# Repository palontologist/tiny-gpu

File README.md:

# tiny-gpu

A RISC-V-based GPU implementation in Verilog designed to explore and implement high-performance GPU architectures—from scalar cores and vector SIMD to cache hierarchies and graphics rasterization.

Built with ~20 files of fully documented Verilog, the project evolves through 7 development milestones: RV32IM scalar core, INT4/FP32 ML extensions, sparsity-aware execution, out-of-order ROB, L1 cache, graphics pipeline, and 128-bit vector SIMD. It includes verified matrix addition/multiplication and vector kernels with full simulation and execution traces.

### Table of Contents

- [Overview](#overview)
- [Architecture](#architecture)
  - [GPU](#gpu)
  - [Memory](#memory)
  - [Core](#core)
- [Hardware Implementation](#hardware-implementation)
- [ISA](#isa)
  - [Base RV32IM](#base-rv32im)
  - [Custom Extensions](#custom-extensions)
  - [Register File](#register-file)
- [Execution](#execution)
  - [Pipeline Stages](#pipeline-stages)
  - [Out-of-Order Execution](#out-of-order-execution)
  - [Sparsity-Aware Execution](#sparsity-aware-execution)
  - [Thread](#thread)
- [Kernels](#kernels)
  - [Matrix Addition](#matrix-addition-rv32i)
  - [Matrix Multiplication](#matrix-multiplication-rv32im)
  - [Vector DP4A](#vector-dp4a-phase-7--custom2)
- [Simulation](#simulation)
- [Optimizations](#optimizations)
  - [Implemented](#implemented-optimizations)
  - [Future](#future-optimizations)
- [Unified CPU/GPU Architecture (Approach B: RVV) & Modular Extensibility](#unified-cpugpu-architecture-approach-b-rvv--modular-extensibility)
- [Next Steps](#next-steps)

# Overview

While there are many resources for learning CPU architecture, GPU internals remain largely proprietary and opaque. Open-source implementations like [Miaow](https://github.com/VerticalResearchGroup/miaow) and [VeriGPU](https://github.com/hughperkins/VeriGPU/tree/main) are excellent but highly complex.

`tiny-gpu` is designed to bridge this gap, providing a transparent and modular reference implementation of a GPU's core logic.

## What is tiny-gpu?

> [!IMPORTANT]
> **tiny-gpu** is a RISC-V-based GPU implementation focused on the fundamental principles of GPGPU and ML-accelerator architectures. It emphasizes the general mechanisms of data parallelism and memory throughput rather than graphics-specific hardware.

The project is structured into 7 development milestones:

- **Phase 1**: RV32IM scalar core (RISC-V base ISA)
- **Phase 2**: INT4/FP32 custom extensions for ML inference
- **Phase 3**: Sparsity-aware execution (zero-skip for power efficiency)
- **Phase 4**: Out-of-order execution with Tomasulo-style ROB
- **Phase 5**: Per-thread L1 data cache (2-way set-associative)
- **Phase 6**: Graphics pipeline (rasterizer + texture unit + framebuffer)
- **Phase 7**: 128-bit vector extensions (INT8/INT4 SIMD, FP32 stubs)

The project explores four primary domains:
1. **Architecture** - Defining the core elements of a GPU and their interconnections.
2. **Parallelization** - Implementing the SIMD programming model in hardware.
3. **Memory** - Managing bandwidth constraints and latency via caching.
4. **ML Acceleration** - Utilizing vector units and quantization for efficient inference.

# Architecture

## GPU

`tiny-gpu` executes a single kernel at a time through the following process:
1. Load global program memory with kernel code (32-bit RV32IM instructions).
2. Load data memory with the necessary data (32-bit scalar or 128-bit vector).
3. Specify the thread count in the device control register.
4. Launch the kernel via the start signal.

The GPU architecture consists of:
1. Device control register
2. Dispatcher
3. Compute cores (each containing a ROB, L1 cache, and vector units)
4. Memory controllers for data and program memory
5. L1 data cache (per-thread, 2-way set-associative)

### GPU Parameters

| Parameter | Default | Description |
|-----------|---------|-------------|
| `NUM_CORES` | 2 | Number of compute cores |
| `THREADS_PER_BLOCK` | 4 | SIMD width per core |
| `ROB_DEPTH` | 16 | Reorder buffer entries per core |
| `L1_SETS` | 16 | L1 cache sets per thread |
| `VECTOR_ENABLE` | 1 | 128-bit data bus (0 = 32-bit legacy) |

### Device Control Register
The device control register stores metadata for kernel execution, primarily the `thread_count`—the total number of threads launched for the active kernel.

### Dispatcher
The dispatcher manages the distribution of threads to compute cores. It organizes threads into **blocks** and assigns them to available cores. Once all blocks are processed, the dispatcher signals kernel completion.

## Memory

`tiny-gpu` interfaces with an external global memory, separating data and program memory for architectural simplicity.

### Global Memory
- **Data Memory:** 8-bit addressability (256 word-addressable rows). Supports 32-bit scalar data or 128-bit vector data (when `VECTOR_ENABLE=1`).
- **Program Memory:** 8-bit addressability (256 word-addressable rows) storing 32-bit RV32IM instructions.

### Memory Controllers
The memory controllers manage outgoing requests from the compute cores, throttling access based on external memory bandwidth and relaying responses back to the requesting resource.

### L1 Data Cache
To mitigate global memory latency, each thread utilizes a **private L1 data cache** (Phase 5):
- **Organization:** 2-way set-associative (16 sets by default).
- **Policy:** Write-through (no dirty bits required).
- **Latency:** 1 cycle hit; memory-controller round-trip + 1 fill cycle for misses.
- **Replacement:** LRU (Least Recently Used) policy per set.

## Core

Each core manages a block of threads. To maximize resource utilization, the core provides a dedicated ALU, LSU, PC, scalar/vector register files, and L1 cache for each thread.

### Scheduler
A single scheduler manages the execution of threads through a 7-stage pipeline. The scheduler executes one block to completion, processing all threads in-sync and sequentially.

- **Sparsity-Aware Execution (Phase 3):** If all threads in a warp have zero-valued operands for an ALU operation, the scheduler skips the EXECUTE stage and writes zero directly to save power and cycles.
- **ROB Hazard Management (Phase 4):** Before advancing past the REQUEST stage, the scheduler checks for unresolved in-flight writes in the ROB. The pipeline stalls until the hazard clears or the value is forwarded.

### Reorder Buffer (ROB)
Phase 4 introduces a Tomasulo-style ROB for out-of-order execution:
- **In-order allocation** at the tail, **in-order commit** at the head.
- **Out-of-order writeback** upon execution unit completion.
- **Hazard detection** and **Result forwarding** to minimize pipeline stalls.

Each ROB entry covers one warp-level instruction, storing per-thread result data for SIMD execution.

### Fetcher
Asynchronously fetches 32-bit instructions from program memory based on the current PC.

### Decoder
Decodes RV32IM instructions into control signals, including:
- **Standard RV32I** opcodes.
- **RV32M** multiply/divide extensions.
- **Custom Opcodes:** `CUSTOM0` (RET), `CUSTOM1` (INT4/FP32), `CUSTOM2` (128-bit vector SIMD).

### Register Files
- **Scalar Registers (RV32):** 32 × 32-bit registers (x0-x31). x0 is hardwired to zero; x13-x15 are read-only special registers (`%blockIdx`, `%blockDim`, `%threadIdx`).
- **Vector Registers (Phase 7):** 16 × 128-bit registers (v0-v15). v0 is hardwired to zero; v13-v15 mirror scalar special registers.

### ALUs
Dedicated arithmetic-logic units per thread for scalar computations:
- **RV32I/M:** Full integer and multiply/divide support.
- **Custom (Phase 2/6):** `DP4A` (INT4 dot-product accumulate) and FP32 stubs.

### Vector ALUs (Phase 7)
Dedicated 128-bit vector ALUs for packed SIMD operations:
- **INT8:** 16-lane add, multiply, and multiply-accumulate.
- **INT4:** 4 × (8 × INT4 signed DP4A) for 32-bit accumulation.
- **FP32:** 4-lane add, multiply, and FMA (stubs).

### LSUs
Load-Store Units manage access to global data memory, supporting standard RV32I operations and Phase 7 vector extensions (`VLW.Q`, `VSW.Q` for 128-bit quad-word transfers).

### PCs
Dedicated program counters per thread. The PC increments by 4 for standard instructions or jumps to target addresses during branch/jump operations.

### Graphics Pipeline (Phase 6)
- **Rasterizer:** Scan-line tile rasterizer with barycentric interpolation (16.16 fixed-point).
- **Texture Unit:** Bilinear filtering with INT8 texels (8.8 fixed-point UV).
- **Framebuffer Interface:** Connects rasterizer output to display memory.

# Hardware Implementation

To move `tiny-gpu` from simulation to physical hardware, a custom carrier board has been designed. All design files, schematics, and assembly guides can be found in the [`/fpga_carrier_board_files`](/home/palontologist/Downloads/dev/tiny-gpu/fpga_carrier_board_files) directory.

### Target Platform
- **FPGA:** AMD Xilinx Artix-7 (XC7A100T-2FGG484I)
- **Memory:** DDR3L x16 (MT41K256M16TW-107:P) for high-bandwidth data access.
- **Video Output:** HDMI 1.4 via SII9022A transmitter.
- **Power:** USB-C PD input with multi-rail voltage regulation (1.0V, 1.8V, 1.35V, 3.3V).

### Design Workflow
The PCB was developed using a code-first approach via **Solder CLI**, allowing for rapid iteration of the 128-bit memory bus and signal integrity optimization. The final design is compatible with KiCad.

### Assembly & Bring-up
A detailed assembly guide (`fpga_carrier_board_GUIDE.md`) is provided, covering the 3D printing of enclosure mounts, BGA soldering of the FPGA and RAM, and the step-by-step bring-up process using a JTAG debugger.

# ISA

The architecture implements the **RV32IM** base ISA with custom extensions for GPU and ML workloads.

## Base RV32IM
Full support for standard RISC-V integer (`I`) and multiply/divide (`M`) instructions (LUI, AUIPC, JAL, JALR, BRANCH, LOAD, STORE, OP-IMM, OP, SYSTEM, MUL, DIV, etc.).

## Custom Extensions

| Opcode | Name | Description |
|--------|------|-------------|
| `CUSTOM0` | `RET` | Return from kernel execution |
| `CUSTOM1` | `DP4A` | INT4 4-element dot product with 32-bit accumulation |
| `CUSTOM1` | `FADD` / `FMUL` / `FFMA` | Single-precision floating point arithmetic stubs |
| `CUSTOM2` | `VADD` / `VMUL` / `VMAC` | 128-bit packed INT8 vector operations |
| `CUSTOM2` | `VDP4A` | 128-bit packed INT4 dot product accumulate |
| `CUSTOM2` | `VLW.Q` / `VSW.Q` | 128-bit vector quad-word memory load/store |

## Register File

- **Scalar Registers:** 32 registers (`x0` through `x31`).
  - `x0`: Constant 0
  - `x13`: Read-only `%blockIdx`
  - `x14`: Read-only `%blockDim`
  - `x15`: Read-only `%threadIdx`
- **Vector Registers:** 16 registers (`v0` through `v15`), each 128 bits wide.

# Execution

## Pipeline Stages

The execution pipeline consists of 7 stages:
1. **FETCH:** Retrieve instruction from program memory.
2. **DECODE:** Decode instruction and identify operand registers.
3. **REQUEST:** Issue memory requests or check for ROB hazards.
4. **WAIT:** Wait for memory data or hazard clearance.
5. **EXECUTE:** Compute ALU / Vector / Branch results (or perform zero-skip).
6. **UPDATE:** Update PC, write back results to register file or ROB.
7. **COMMIT:** In-order commit from ROB to architectural state.

## Out-of-Order Execution
Supported via Tomasulo-style Reorder Buffer (ROB) tracking in-flight instructions, resolving RAW hazards, and enabling speculative result forwarding.

## Sparsity-Aware Execution
Skips the execute stage when operands are detected as zero, directly writing zero to destination registers and cutting dynamic power consumption.

## Thread
Threads execute in SIMD blocks where each lane shares instruction flow but maintains private register and cache state.

# Kernels

### Matrix Addition (RV32I)
Demonstrates standard RISC-V scalar instructions distributed across threads to compute element-wise addition over matrix buffers.

### Matrix Multiplication (RV32IM)
Leverages RV32M hardware multiplier extensions for high-throughput tile-based matrix multiplication.

### Vector DP4A (Phase 7 / CUSTOM2)
Utilizes 128-bit vector units to compute quantized INT4 dot products with 32-bit accumulation for neural network linear layers.

# Simulation

### Prerequisites
- `iverilog` (Icarus Verilog)
- Python 3 & `cocotb`
- `gnumake`

```bash
# Using Nix
nix-shell -p iverilog python3 python3Packages.cocotb gnumake
```

### Run Tests
```bash
make test_matadd    # Scalar matrix addition
make test_matmul    # Scalar matrix multiplication + vector DP4A
```

# Optimizations

### Implemented Optimizations
- **INT4 Quantization:** Efficient ML inference with reduced precision.
- **Sparsity-Aware Skip:** Dynamic power optimization for zero operands.
- **Tomasulo ROB:** Dynamic out-of-order execution with result forwarding.
- **Per-Thread L1 Cache:** Mitigates global memory latency.
- **Vector SIMD:** 128-bit data bus with packed INT8/INT4 and FP32 stubs.

### Future Optimizations
- **Warp Scheduling:** Implement multi-warp concurrency per core.
- **Branch Divergence:** Handle divergent execution paths.
- **FP32 Silicon:** Replace stubs with IEEE-754 compliant FP IP.
- **Physical Bring-up:** Finalize fabrication and test the `tiny-gpu` on the custom Artix-7 carrier board.

# Unified CPU/GPU Architecture (Approach B: RVV) & Modular Extensibility

As `tiny-gpu` evolves, the architectural roadmap moves toward a **Unified RISC-V CPU/GPU Architecture** based on the standard **RISC-V Vector Extension (RVV 1.0)** and **Simple-V** dynamic vectorization.

### Why Unified RVV (Approach B)?
- **Vector-Length Agnostic (VLA):** Binary executables automatically scale across hardware vector widths ($VLEN$) without recompilation.
- **Standard Toolchains:** Upstream LLVM and GCC support, eliminating proprietary SIMT compiler forks.
- **Vulkan / SPIR-V Support:** Seamless translation of graphics shaders directly into standard vector instructions.

### Modular Extensibility & eGPU Scaling
- **Seamless Laptop-to-eGPU Offloading:** Identical binaries run locally on a low-power laptop core ($VLEN=128\text{b}$) and scale effortlessly to an external accelerator ($VLEN=2048\text{b}\text{ to }4096\text{b}$).
- **Coherent Interconnects:** Interfacing over CXL.mem/CXL.cache or TileLink/PCIe eliminates explicit PCIe data copies (`cudaMemcpy`) in favor of unified virtual memory.

📖 **Detailed Architectural Specification:** For the complete design document, pipeline diagrams, and roadmap, see [`docs/unified-cpu-gpu-rvv.md`](docs/unified-cpu-gpu-rvv.md).

## Next Steps
Contributors are welcome to help with the TODO list or submit PRs for new optimizations!

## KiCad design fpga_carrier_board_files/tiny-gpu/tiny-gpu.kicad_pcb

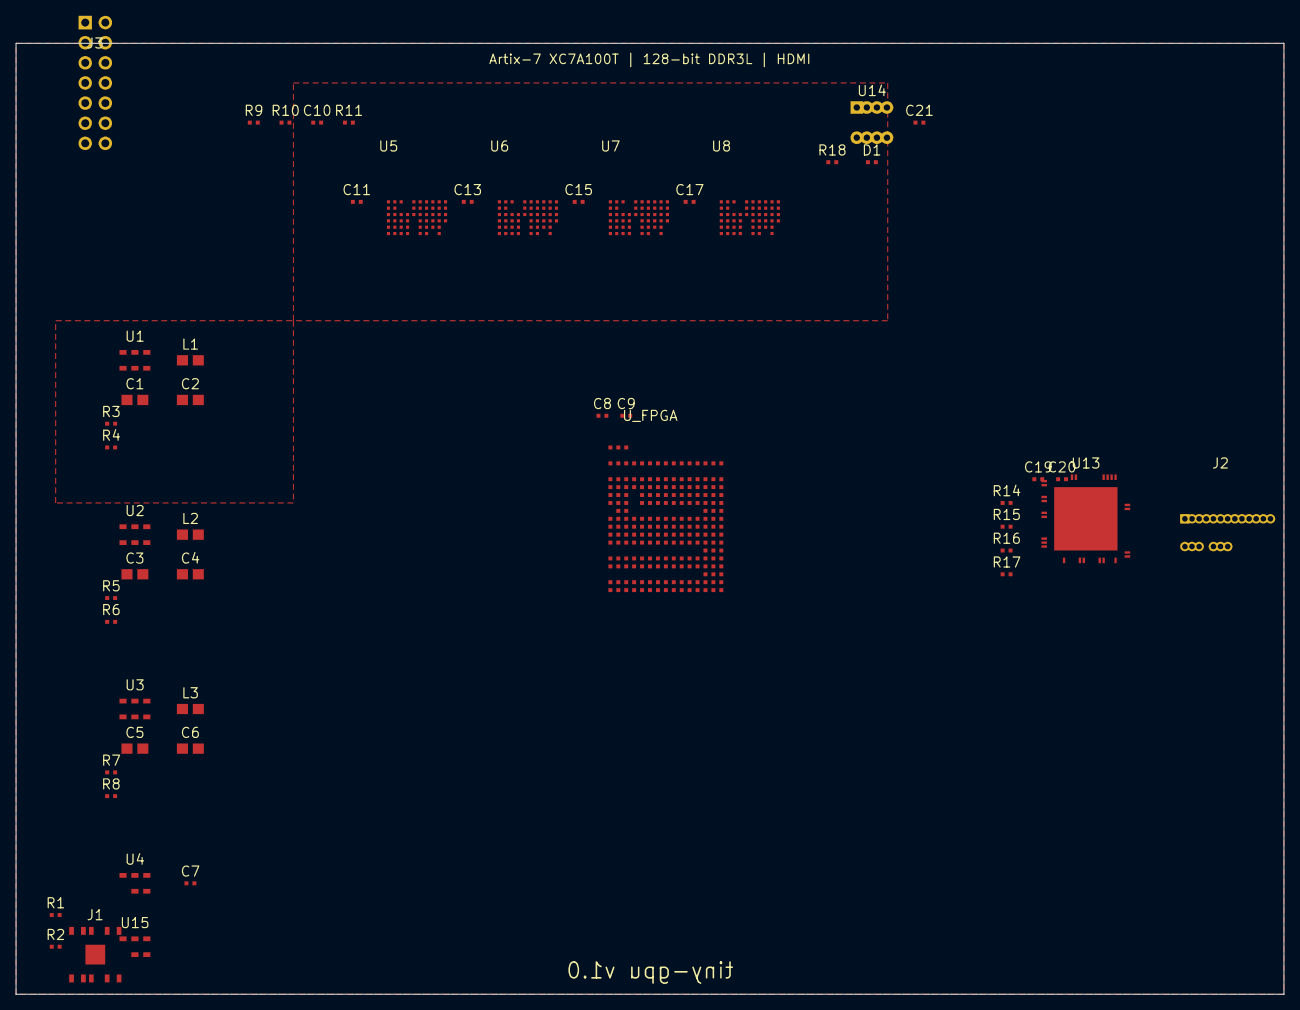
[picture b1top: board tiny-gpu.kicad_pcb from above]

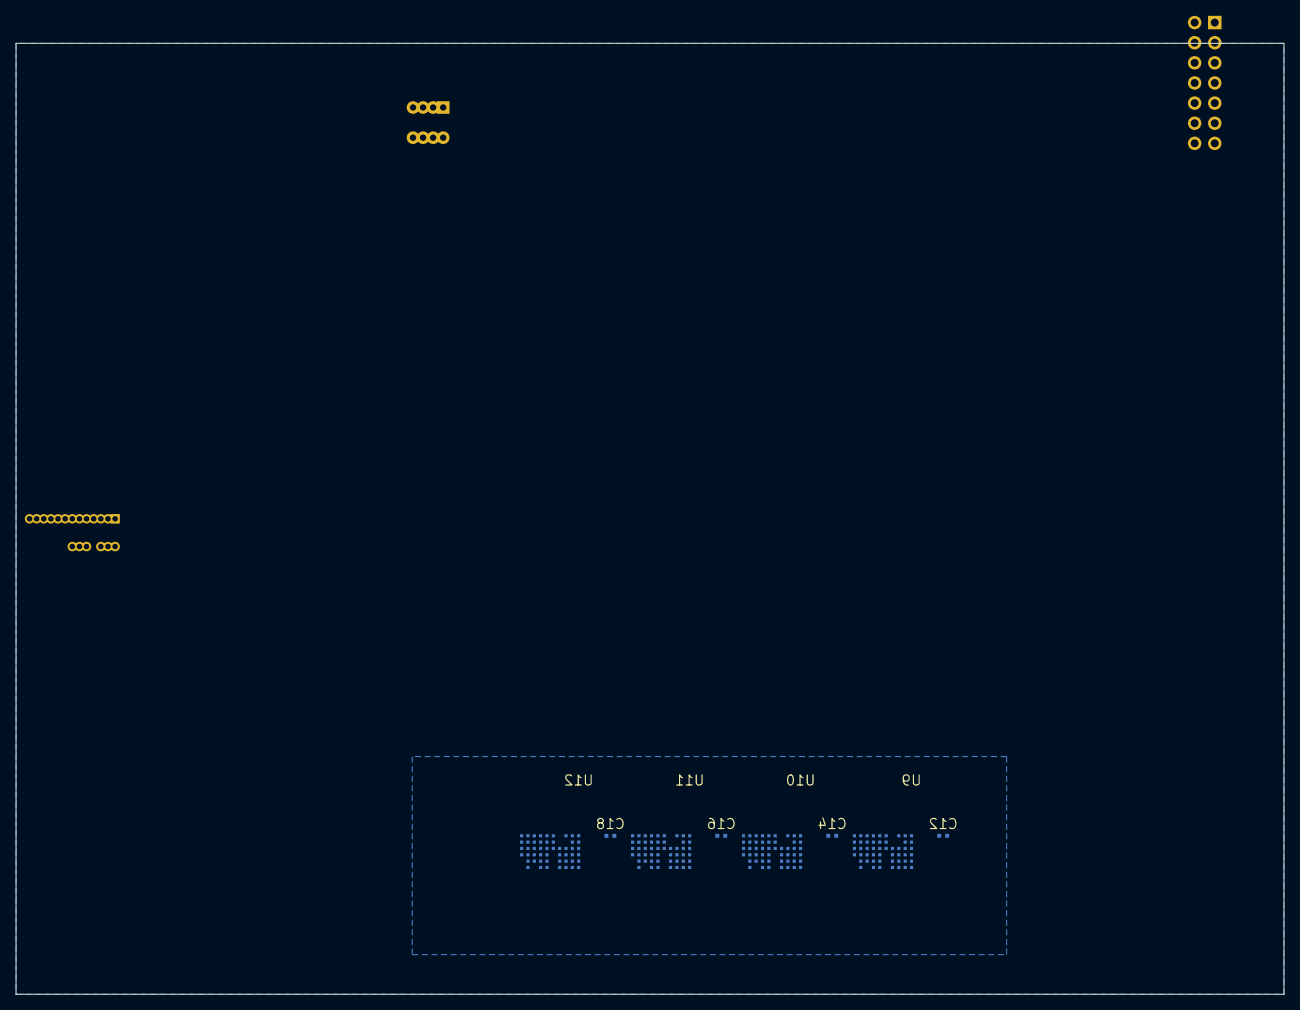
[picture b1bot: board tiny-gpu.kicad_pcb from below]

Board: 4 copper layers, 160.0 x 120.0 mm, 60 parts (8 on the bottom side), 226 nets, no tracks yet.

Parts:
C1, C2, C3, C4, C5, C6: C_0805_2012Metric
C7, C8, C9, C10, C11, C12, C13, C14, C15, C16, C17, C18, C19, C20, C21: C_0402_1005Metric
D1: LED_0402_1005Metric
J1: USB_C_Receptacle_GCT_USB4135-GF-A_Vertical
J2: HDMI_TypeA_Molex_2171100001_Horizontal
J3: PinHeader_2x07_P2.54mm_Vertical
L1, L2, L3: L_0805_2012Metric
R1, R2, R3, R4, R5, R6, R7, R8, R9, R10, R11, R14, R15, R16, R17, R18: R_0402_1005Metric
U1, U2, U3: SOT-23-6
U4, U15: SOT-25
U5, U6, U7, U8, U9, U10, U11, U12: BGA-96_9x12_8.0x10.5mm_Layout9x11_P0.8mm
U13: QFN-72-1EP_10x10mm_P0.5mm_EP8x8mm
U14: SOIC-8_3.9x4.9mm_P1.27mm
U_FPGA: BGA-484_23x23_21.0x21.0mm_Layout22x22_P0.95mm

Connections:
3V3_IO: C7.1, C19.1, C21.1, J2.18, J3.11, R14.1, R15.1, R16.1, R17.1, U4.4, U13.2, U14.3, U14.7, U14.8, U_FPGA.VCCO_14, U_FPGA.VCCO_15
CC1: J1.A5, R1.1
CC2: J1.B5, R2.1
DDR_A0: U5.A0, U6.A0, U7.A0, U8.A0, U9.A0, U10.A0, U11.A0, U12.A0, U_FPGA.DDR_A0
DDR_A1: U5.A1, U6.A1, U7.A1, U8.A1, U9.A1, U10.A1, U11.A1, U12.A1, U_FPGA.DDR_A1
DDR_A2: U5.A2, U6.A2, U7.A2, U8.A2, U9.A2, U10.A2, U11.A2, U12.A2, U_FPGA.DDR_A2
DDR_A3: U5.A3, U6.A3, U7.A3, U8.A3, U9.A3, U10.A3, U11.A3, U12.A3, U_FPGA.DDR_A3
DDR_A4: U5.A4, U6.A4, U7.A4, U8.A4, U9.A4, U10.A4, U11.A4, U12.A4, U_FPGA.DDR_A4
DDR_A5: U5.A5, U6.A5, U7.A5, U8.A5, U9.A5, U10.A5, U11.A5, U12.A5, U_FPGA.DDR_A5
DDR_A6: U5.A6, U6.A6, U7.A6, U8.A6, U9.A6, U10.A6, U11.A6, U12.A6, U_FPGA.DDR_A6
DDR_A7: U5.A7, U6.A7, U7.A7, U8.A7, U9.A7, U10.A7, U11.A7, U12.A7, U_FPGA.DDR_A7
DDR_A8: U5.A8, U6.A8, U7.A8, U8.A8, U9.A8, U10.A8, U11.A8, U12.A8, U_FPGA.DDR_A8
DDR_A9: U5.A9, U6.A9, U7.A9, U8.A9, U9.A9, U10.A9, U11.A9, U12.A9, U_FPGA.DDR_A9
DDR_A10: U5.A10, U6.A10, U7.A10, U8.A10, U9.A10, U10.A10, U11.A10, U12.A10, U_FPGA.DDR_A10
DDR_A11: U5.A11, U6.A11, U7.A11, U8.A11, U9.A11, U10.A11, U11.A11, U12.A11, U_FPGA.DDR_A11
DDR_A12: U5.A12, U6.A12, U7.A12, U8.A12, U9.A12, U10.A12, U11.A12, U12.A12, U_FPGA.DDR_A12
DDR_A13: U5.A13, U6.A13, U7.A13, U8.A13, U9.A13, U10.A13, U11.A13, U12.A13, U_FPGA.DDR_A13
DDR_BA0: U5.BA0, U6.BA0, U7.BA0, U8.BA0, U9.BA0, U10.BA0, U11.BA0, U12.BA0, U_FPGA.DDR_BA0
DDR_BA1: U5.BA1, U6.BA1, U7.BA1, U8.BA1, U9.BA1, U10.BA1, U11.BA1, U12.BA1, U_FPGA.DDR_BA1
DDR_BA2: U5.BA2, U6.BA2, U7.BA2, U8.BA2, U9.BA2, U10.BA2, U11.BA2, U12.BA2, U_FPGA.DDR_BA2
DDR_CAS_N: U5.CASN, U6.CASN, U7.CASN, U8.CASN, U9.CASN, U10.CASN, U11.CASN, U12.CASN, U_FPGA.DDR_CASN
DDR_CKE: U5.CKE, U6.CKE, U7.CKE, U8.CKE, U9.CKE, U10.CKE, U11.CKE, U12.CKE, U_FPGA.DDR_CKE
DDR_CKN: U5.CKN, U6.CKN, U7.CKN, U8.CKN, U9.CKN, U10.CKN, U11.CKN, U12.CKN, U_FPGA.DDR_CKN
DDR_CKP: U5.CKP, U6.CKP, U7.CKP, U8.CKP, U9.CKP, U10.CKP, U11.CKP, U12.CKP, U_FPGA.DDR_CKP
DDR_CS_N: U5.CSN, U6.CSN, U7.CSN, U8.CSN, U9.CSN, U10.CSN, U11.CSN, U12.CSN, U_FPGA.DDR_CSN
DDR_DM0: U5.DM, U_FPGA.DDR_DM0
DDR_DM1: U6.DM, U_FPGA.DDR_DM1
DDR_DM2: U7.DM, U_FPGA.DDR_DM2
DDR_DM3: U8.DM, U_FPGA.DDR_DM3
DDR_DM4: U9.DM, U_FPGA.DDR_DM4
DDR_DM5: U10.DM, U_FPGA.DDR_DM5
DDR_DM6: U11.DM, U_FPGA.DDR_DM6
DDR_DM7: U12.DM, U_FPGA.DDR_DM7
DDR_DQ0: U5.DQ0, U_FPGA.DDR_DQ0
DDR_DQ1: U5.DQ1, U_FPGA.DDR_DQ1
DDR_DQ2: U5.DQ2, U_FPGA.DDR_DQ2
DDR_DQ3: U5.DQ3, U_FPGA.DDR_DQ3
DDR_DQ4: U5.DQ4, U_FPGA.DDR_DQ4
DDR_DQ5: U5.DQ5, U_FPGA.DDR_DQ5
DDR_DQ6: U5.DQ6, U_FPGA.DDR_DQ6
DDR_DQ7: U5.DQ7, U_FPGA.DDR_DQ7
DDR_DQ8: U5.DQ8, U_FPGA.DDR_DQ8
DDR_DQ9: U5.DQ9, U_FPGA.DDR_DQ9
DDR_DQ10: U5.DQ10, U_FPGA.DDR_DQ10
DDR_DQ11: U5.DQ11, U_FPGA.DDR_DQ11
DDR_DQ12: U5.DQ12, U_FPGA.DDR_DQ12
DDR_DQ13: U5.DQ13, U_FPGA.DDR_DQ13
DDR_DQ14: U5.DQ14, U_FPGA.DDR_DQ14
DDR_DQ15: U5.DQ15, U_FPGA.DDR_DQ15
DDR_DQ16: U6.DQ0, U_FPGA.DDR_DQ16
DDR_DQ17: U6.DQ1, U_FPGA.DDR_DQ17
DDR_DQ18: U6.DQ2, U_FPGA.DDR_DQ18
DDR_DQ19: U6.DQ3, U_FPGA.DDR_DQ19
DDR_DQ20: U6.DQ4, U_FPGA.DDR_DQ20
DDR_DQ21: U6.DQ5, U_FPGA.DDR_DQ21
DDR_DQ22: U6.DQ6, U_FPGA.DDR_DQ22
DDR_DQ23: U6.DQ7, U_FPGA.DDR_DQ23
DDR_DQ24: U6.DQ8, U_FPGA.DDR_DQ24
DDR_DQ25: U6.DQ9, U_FPGA.DDR_DQ25
DDR_DQ26: U6.DQ10, U_FPGA.DDR_DQ26
DDR_DQ27: U6.DQ11, U_FPGA.DDR_DQ27
DDR_DQ28: U6.DQ12, U_FPGA.DDR_DQ28
DDR_DQ29: U6.DQ13, U_FPGA.DDR_DQ29
DDR_DQ30: U6.DQ14, U_FPGA.DDR_DQ30
DDR_DQ31: U6.DQ15, U_FPGA.DDR_DQ31
DDR_DQ32: U7.DQ0, U_FPGA.DDR_DQ32
DDR_DQ33: U7.DQ1, U_FPGA.DDR_DQ33
DDR_DQ34: U7.DQ2, U_FPGA.DDR_DQ34
DDR_DQ35: U7.DQ3, U_FPGA.DDR_DQ35
DDR_DQ36: U7.DQ4, U_FPGA.DDR_DQ36
DDR_DQ37: U7.DQ5, U_FPGA.DDR_DQ37
DDR_DQ38: U7.DQ6, U_FPGA.DDR_DQ38
DDR_DQ39: U7.DQ7, U_FPGA.DDR_DQ39
DDR_DQ40: U7.DQ8, U_FPGA.DDR_DQ40
DDR_DQ41: U7.DQ9, U_FPGA.DDR_DQ41
DDR_DQ42: U7.DQ10, U_FPGA.DDR_DQ42
DDR_DQ43: U7.DQ11, U_FPGA.DDR_DQ43
DDR_DQ44: U7.DQ12, U_FPGA.DDR_DQ44
DDR_DQ45: U7.DQ13, U_FPGA.DDR_DQ45
DDR_DQ46: U7.DQ14, U_FPGA.DDR_DQ46
DDR_DQ47: U7.DQ15, U_FPGA.DDR_DQ47
DDR_DQ48: U8.DQ0, U_FPGA.DDR_DQ48
DDR_DQ49: U8.DQ1, U_FPGA.DDR_DQ49
DDR_DQ50: U8.DQ2, U_FPGA.DDR_DQ50
DDR_DQ51: U8.DQ3, U_FPGA.DDR_DQ51
DDR_DQ52: U8.DQ4, U_FPGA.DDR_DQ52
DDR_DQ53: U8.DQ5, U_FPGA.DDR_DQ53
DDR_DQ54: U8.DQ6, U_FPGA.DDR_DQ54
DDR_DQ55: U8.DQ7, U_FPGA.DDR_DQ55
DDR_DQ56: U8.DQ8, U_FPGA.DDR_DQ56
DDR_DQ57: U8.DQ9, U_FPGA.DDR_DQ57
DDR_DQ58: U8.DQ10, U_FPGA.DDR_DQ58
DDR_DQ59: U8.DQ11, U_FPGA.DDR_DQ59
DDR_DQ60: U8.DQ12, U_FPGA.DDR_DQ60
DDR_DQ61: U8.DQ13, U_FPGA.DDR_DQ61
DDR_DQ62: U8.DQ14, U_FPGA.DDR_DQ62
DDR_DQ63: U8.DQ15, U_FPGA.DDR_DQ63
DDR_DQ64: U9.DQ0, U_FPGA.DDR_DQ64
DDR_DQ65: U9.DQ1, U_FPGA.DDR_DQ65
DDR_DQ66: U9.DQ2, U_FPGA.DDR_DQ66
DDR_DQ67: U9.DQ3, U_FPGA.DDR_DQ67
DDR_DQ68: U9.DQ4, U_FPGA.DDR_DQ68
DDR_DQ69: U9.DQ5, U_FPGA.DDR_DQ69
DDR_DQ70: U9.DQ6, U_FPGA.DDR_DQ70
DDR_DQ71: U9.DQ7, U_FPGA.DDR_DQ71
DDR_DQ72: U9.DQ8, U_FPGA.DDR_DQ72
DDR_DQ73: U9.DQ9, U_FPGA.DDR_DQ73
DDR_DQ74: U9.DQ10, U_FPGA.DDR_DQ74
DDR_DQ75: U9.DQ11, U_FPGA.DDR_DQ75
DDR_DQ76: U9.DQ12, U_FPGA.DDR_DQ76
DDR_DQ77: U9.DQ13, U_FPGA.DDR_DQ77
DDR_DQ78: U9.DQ14, U_FPGA.DDR_DQ78
DDR_DQ79: U9.DQ15, U_FPGA.DDR_DQ79
DDR_DQ80: U10.DQ0, U_FPGA.DDR_DQ80
DDR_DQ81: U10.DQ1, U_FPGA.DDR_DQ81
DDR_DQ82: U10.DQ2, U_FPGA.DDR_DQ82
DDR_DQ83: U10.DQ3, U_FPGA.DDR_DQ83
DDR_DQ84: U10.DQ4, U_FPGA.DDR_DQ84
DDR_DQ85: U10.DQ5, U_FPGA.DDR_DQ85
DDR_DQ86: U10.DQ6, U_FPGA.DDR_DQ86
DDR_DQ87: U10.DQ7, U_FPGA.DDR_DQ87
DDR_DQ88: U10.DQ8, U_FPGA.DDR_DQ88
DDR_DQ89: U10.DQ9, U_FPGA.DDR_DQ89
DDR_DQ90: U10.DQ10, U_FPGA.DDR_DQ90
DDR_DQ91: U10.DQ11, U_FPGA.DDR_DQ91
DDR_DQ92: U10.DQ12, U_FPGA.DDR_DQ92
DDR_DQ93: U10.DQ13, U_FPGA.DDR_DQ93
DDR_DQ94: U10.DQ14, U_FPGA.DDR_DQ94
DDR_DQ95: U10.DQ15, U_FPGA.DDR_DQ95
DDR_DQ96: U11.DQ0, U_FPGA.DDR_DQ96
DDR_DQ97: U11.DQ1, U_FPGA.DDR_DQ97
DDR_DQ98: U11.DQ2, U_FPGA.DDR_DQ98
DDR_DQ99: U11.DQ3, U_FPGA.DDR_DQ99
DDR_DQ100: U11.DQ4, U_FPGA.DDR_DQ100
DDR_DQ101: U11.DQ5, U_FPGA.DDR_DQ101
DDR_DQ102: U11.DQ6, U_FPGA.DDR_DQ102
DDR_DQ103: U11.DQ7, U_FPGA.DDR_DQ103
DDR_DQ104: U11.DQ8, U_FPGA.DDR_DQ104
DDR_DQ105: U11.DQ9, U_FPGA.DDR_DQ105
DDR_DQ106: U11.DQ10, U_FPGA.DDR_DQ106
DDR_DQ107: U11.DQ11, U_FPGA.DDR_DQ107
DDR_DQ108: U11.DQ12, U_FPGA.DDR_DQ108
DDR_DQ109: U11.DQ13, U_FPGA.DDR_DQ109
DDR_DQ110: U11.DQ14, U_FPGA.DDR_DQ110
DDR_DQ111: U11.DQ15, U_FPGA.DDR_DQ111
DDR_DQ112: U12.DQ0, U_FPGA.DDR_DQ112
DDR_DQ113: U12.DQ1, U_FPGA.DDR_DQ113
DDR_DQ114: U12.DQ2, U_FPGA.DDR_DQ114
DDR_DQ115: U12.DQ3, U_FPGA.DDR_DQ115
DDR_DQ116: U12.DQ4, U_FPGA.DDR_DQ116
DDR_DQ117: U12.DQ5, U_FPGA.DDR_DQ117
DDR_DQ118: U12.DQ6, U_FPGA.DDR_DQ118
DDR_DQ119: U12.DQ7, U_FPGA.DDR_DQ119
DDR_DQ120: U12.DQ8, U_FPGA.DDR_DQ120
DDR_DQ121: U12.DQ9, U_FPGA.DDR_DQ121
DDR_DQ122: U12.DQ10, U_FPGA.DDR_DQ122
DDR_DQ123: U12.DQ11, U_FPGA.DDR_DQ123
DDR_DQ124: U12.DQ12, U_FPGA.DDR_DQ124
DDR_DQ125: U12.DQ13, U_FPGA.DDR_DQ125
DDR_DQ126: U12.DQ14, U_FPGA.DDR_DQ126
DDR_DQ127: U12.DQ15, U_FPGA.DDR_DQ127
DDR_DQS0N: U5.DQSN, U_FPGA.DDR_DQS0N
DDR_DQS0P: U5.DQSP, U_FPGA.DDR_DQS0P
DDR_DQS1N: U6.DQSN, U_FPGA.DDR_DQS1N
DDR_DQS1P: U6.DQSP, U_FPGA.DDR_DQS1P
DDR_DQS2N: U7.DQSN, U_FPGA.DDR_DQS2N
DDR_DQS2P: U7.DQSP, U_FPGA.DDR_DQS2P
DDR_DQS3N: U8.DQSN, U_FPGA.DDR_DQS3N
DDR_DQS3P: U8.DQSP, U_FPGA.DDR_DQS3P
DDR_DQS4N: U9.DQSN, U_FPGA.DDR_DQS4N
DDR_DQS4P: U9.DQSP, U_FPGA.DDR_DQS4P
DDR_DQS5N: U10.DQSN, U_FPGA.DDR_DQS5N
DDR_DQS5P: U10.DQSP, U_FPGA.DDR_DQS5P
DDR_DQS6N: U11.DQSN, U_FPGA.DDR_DQS6N
DDR_DQS6P: U11.DQSP, U_FPGA.DDR_DQS6P
DDR_DQS7N: U12.DQSN, U_FPGA.DDR_DQS7N
DDR_DQS7P: U12.DQSP, U_FPGA.DDR_DQS7P
DDR_ODT: U5.ODT, U6.ODT, U7.ODT, U8.ODT, U9.ODT, U10.ODT, U11.ODT, U12.ODT, U_FPGA.DDR_ODT
DDR_RAS_N: U5.RASN, U6.RASN, U7.RASN, U8.RASN, U9.RASN, U10.RASN, U11.RASN, U12.RASN, U_FPGA.DDR_RASN
DDR_RESET_N: U5.RESETN, U6.RESETN, U7.RESETN, U8.RESETN, U9.RESETN, U10.RESETN, U11.RESETN, U12.RESETN, U_FPGA.DDR_RESETN
DDR_VREFDQ: C10.1, R9.2, R10.1, U5.VREFDQ, U6.VREFDQ, U7.VREFDQ, U8.VREFDQ, U9.VREFDQ, U10.VREFDQ, U11.VREFDQ, U12.VREFDQ
DDR_WE_N: U5.WEN, U6.WEN, U7.WEN, U8.WEN, U9.WEN, U10.WEN, U11.WEN, U12.WEN, U_FPGA.DDR_WEN
DDR_ZQ: R11.1, U5.ZQ, U6.ZQ, U7.ZQ, U8.ZQ, U9.ZQ, U10.ZQ, U11.ZQ, U12.ZQ
FLASH_CLK: U14.6, U_FPGA.CCLK
FLASH_CS_N: U14.1, U_FPGA.CSIB
FLASH_MISO: U14.2, U_FPGA.DOUT
FLASH_MOSI: U14.5, U_FPGA.DIN
FPGA_DONE: R18.1, U_FPGA.DONE
FPGA_DONE_LED: D1.2, R18.2
FPGA_HDMI_INT_N: R15.2, U13.60
FPGA_PROG_N: J3.13, U_FPGA.PROG
GND: C1.2, C2.2, C3.2, C4.2, C5.2, C6.2, C7.2, C8.2, C9.2, C10.2, C11.2, C12.2, C13.2, C14.2, C15.2, C16.2, C17.2, C18.2, C19.2, C20.2, C21.2, D1.1, J1.A1, J1.A12, J1.B1, J1.B12, J1.S1, J2.2, J2.5, J2.8, J2.11, J2.GND2, J2.GND3, J2.GND4, J3.2, J3.4, J3.6, J3.8, J3.10, J3.12, J3.14, R1.2, R2.2, R4.2, R6.2, R8.2, R10.2, R11.2, U1.4, U2.4, U3.4, U4.2, U5.VSS, U5.VSSQ, U6.VSS, U6.VSSQ, U7.VSS, U7.VSSQ, U8.VSS, U8.VSSQ, U9.VSS, U9.VSSQ, U10.VSS, U10.VSSQ, U11.VSS, U11.VSSQ, U12.VSS, U12.VSSQ, U13.3, U13.EP, U14.4, U15.2, U_FPGA.GND
HDMI_D0N: U13.41, U_FPGA.HDMI_D0N
HDMI_D0P: U13.40, U_FPGA.HDMI_D0P
HDMI_DE: U13.33, U_FPGA.HDMI_DE
HDMI_HPD: J2.19, U13.57
HDMI_HSYNC: U13.32, U_FPGA.HDMI_HSYNC
HDMI_PCLK: U13.30, U_FPGA.HDMI_PCLK
HDMI_RESET_N: R14.2, U13.61
HDMI_SCL: J2.15, R16.2, U13.55, U13.65, U_FPGA.HDMI_SCL
HDMI_SDA: J2.16, R17.2, U13.56, U13.66, U_FPGA.HDMI_SDA
HDMI_VSYNC: U13.31, U_FPGA.HDMI_VSYNC
JTAG_SRST: J3.9, U_FPGA.SRST
JTAG_TCK: J3.1, U_FPGA.TCK
JTAG_TDI: J3.3, U_FPGA.TDI
JTAG_TDO: J3.5, U_FPGA.TDO
JTAG_TMS: J3.7, U_FPGA.TMS
TMDS_TX0N: J2.9, U13.19
TMDS_TX0P: J2.7, U13.18
TMDS_TX1N: J2.6, U13.15
TMDS_TX1P: J2.4, U13.14
TMDS_TX2N: J2.3, U13.11
TMDS_TX2P: J2.1, U13.10
TMDS_TXCN: J2.12, U13.23
TMDS_TXCP: J2.10, U13.22
VBUS_5V: C1.1, C3.1, C5.1, J1.A4, J1.A9, J1.B4, J1.B9, U1.1, U1.2, U2.1, U2.2, U3.1, U3.2, U4.1
VCC12: C20.1, U13.1, U15.4
VCCAUX: C4.1, C9.1, L2.2, R5.1, U1.5, U2.6, U3.5, U15.1, U15.3, U_FPGA.VCCAUX
VCCAUX_FB2: R5.2, R6.1
VCCAUX_SW: L2.1, U2.3
VCCINT: C2.1, C8.1, L1.2, R3.1, U1.6, U2.5, U_FPGA.VCCBRAM, U_FPGA.VCCINT
VCCINT_FB1: R3.2, R4.1
VCCINT_SW: L1.1, U1.3
VCCO_DDR: C6.1, C11.1, C12.1, C13.1, C14.1, C15.1, C16.1, C17.1, C18.1, L3.2, R7.1, R9.1, U3.6, U4.3, U5.VDD, U5.VDDQ, U6.VDD, U6.VDDQ, U7.VDD, U7.VDDQ, U8.VDD, U8.VDDQ, U9.VDD, U9.VDDQ, U10.VDD, U10.VDDQ, U11.VDD, U11.VDDQ, U12.VDD, U12.VDDQ, U_FPGA.VCCO_0, U_FPGA.VCCO_34, U_FPGA.VCCO_35
VCODDR_FB3: R7.2, R8.1
VCODDR_SW: L3.1, U3.3

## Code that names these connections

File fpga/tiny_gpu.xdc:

## ==============================================================================
## tiny-gpu Xilinx Design Constraints (XDC)
## Target: AMD Xilinx Artix-7 (XC7A100T-2FGG484I)
## ==============================================================================

## -----------------------------------------------------------------------------
## 1. Primary Clock & Reset Constraints
## -----------------------------------------------------------------------------
## 50 MHz Master Oscillator Input
set_property -dict { PACKAGE_PIN R4    IOSTANDARD LVCMOS33 } [get_ports { sys_clk_50m }];
create_clock -period 20.000 -name sys_clk_50m -waveform {0.000 10.000} [get_ports { sys_clk_50m }];

## Active-Low Asynchronous Hardware Reset (Pushbutton / USB-C PD power-good)
set_property -dict { PACKAGE_PIN U7    IOSTANDARD LVCMOS33 } [get_ports { rst_n }];

## -----------------------------------------------------------------------------
## 2. Derived Clock Networks & Clock Domain Crossings (CDC)
## -----------------------------------------------------------------------------
## Core Processing Clock: 50.0 MHz (Period: 20.0 ns)
## Display Pixel Clock:  25.175 MHz (Period: 39.722 ns - 640x480 @ 60Hz)
## DDR3L Memory Interface Clock: 100.0 MHz (Period: 10.0 ns)

set_clock_groups -asynchronous \
    -group [get_clocks -include_generated_clocks sys_clk_50m] \
    -group [get_clocks -include_generated_clocks -filter {NAME =~ *clk_pixel*}] \
    -group [get_clocks -include_generated_clocks -filter {NAME =~ *clk_mem*}]

## -----------------------------------------------------------------------------
## 3. Status & Diagnostic LEDs
## -----------------------------------------------------------------------------
set_property -dict { PACKAGE_PIN T14   IOSTANDARD LVCMOS33 } [get_ports { led_kernel_done }];
set_property -dict { PACKAGE_PIN T15   IOSTANDARD LVCMOS33 } [get_ports { led_core_busy   }];
set_property -dict { PACKAGE_PIN T16   IOSTANDARD LVCMOS33 } [get_ports { led_cache_hit   }];
set_property -dict { PACKAGE_PIN U16   IOSTANDARD LVCMOS33 } [get_ports { led_heartbeat   }];

## -----------------------------------------------------------------------------
## 4. HDMI 1.4 Video Interface (SII9022A Transmitter / Parallel RGB)
## -----------------------------------------------------------------------------
set_property -dict { PACKAGE_PIN W18   IOSTANDARD LVCMOS33 } [get_ports { hdmi_clk }];
set_property -dict { PACKAGE_PIN V17   IOSTANDARD LVCMOS33 } [get_ports { hdmi_hsync }];
set_property -dict { PACKAGE_PIN W17   IOSTANDARD LVCMOS33 } [get_ports { hdmi_vsync }];
set_property -dict { PACKAGE_PIN U17   IOSTANDARD LVCMOS33 } [get_ports { hdmi_de }];

## 24-bit RGB Data Bus (8:8:8)
set_property -dict { PACKAGE_PIN Y18   IOSTANDARD LVCMOS33 } [get_ports { hdmi_d[0] }];  # B0
set_property -dict { PACKAGE_PIN Y19   IOSTANDARD LVCMOS33 } [get_ports { hdmi_d[1] }];  # B1
set_property -dict { PACKAGE_PIN AA18  IOSTANDARD LVCMOS33 } [get_ports { hdmi_d[2] }];  # B2
set_property -dict { PACKAGE_PIN AA19  IOSTANDARD LVCMOS33 } [get_ports { hdmi_d[3] }];  # B3
set_property -dict { PACKAGE_PIN AB20  IOSTANDARD LVCMOS33 } [get_ports { hdmi_d[4] }];  # B4
set_property -dict { PACKAGE_PIN AB21  IOSTANDARD LVCMOS33 } [get_ports { hdmi_d[5] }];  # B5
set_property -dict { PACKAGE_PIN AB22  IOSTANDARD LVCMOS33 } [get_ports { hdmi_d[6] }];  # B6
set_property -dict { PACKAGE_PIN AA21  IOSTANDARD LVCMOS33 } [get_ports { hdmi_d[7] }];  # B7

set_property -dict { PACKAGE_PIN V18   IOSTANDARD LVCMOS33 } [get_ports { hdmi_d[8] }];  # G0
set_property -dict { PACKAGE_PIN V19   IOSTANDARD LVCMOS33 } [get_ports { hdmi_d[9] }];  # G1
set_property -dict { PACKAGE_PIN U20   IOSTANDARD LVCMOS33 } [get_ports { hdmi_d[10] }]; # G2
set_property -dict { PACKAGE_PIN U21   IOSTANDARD LVCMOS33 } [get_ports { hdmi_d[11] }]; # G3
set_property -dict { PACKAGE_PIN T20   IOSTANDARD LVCMOS33 } [get_ports { hdmi_d[12] }]; # G4
set_property -dict { PACKAGE_PIN T21   IOSTANDARD LVCMOS33 } [get_ports { hdmi_d[13] }]; # G5
set_property -dict { PACKAGE_PIN R18   IOSTANDARD LVCMOS33 } [get_ports { hdmi_d[14] }]; # G6
set_property -dict { PACKAGE_PIN P18   IOSTANDARD LVCMOS33 } [get_ports { hdmi_d[15] }]; # G7

set_property -dict { PACKAGE_PIN N17   IOSTANDARD LVCMOS33 } [get_ports { hdmi_d[16] }]; # R0
set_property -dict { PACKAGE_PIN N18   IOSTANDARD LVCMOS33 } [get_ports { hdmi_d[17] }]; # R1
set_property -dict { PACKAGE_PIN M18   IOSTANDARD LVCMOS33 } [get_ports { hdmi_d[18] }]; # R2
set_property -dict { PACKAGE_PIN L18   IOSTANDARD LVCMOS33 } [get_ports { hdmi_d[19] }]; # R3
set_property -dict { PACKAGE_PIN K17   IOSTANDARD LVCMOS33 } [get_ports { hdmi_d[20] }]; # R4
set_property -dict { PACKAGE_PIN J17   IOSTANDARD LVCMOS33 } [get_ports { hdmi_d[21] }]; # R5
set_property -dict { PACKAGE_PIN H18   IOSTANDARD LVCMOS33 } [get_ports { hdmi_d[22] }]; # R6
set_property -dict { PACKAGE_PIN G18   IOSTANDARD LVCMOS33 } [get_ports { hdmi_d[23] }]; # R7

## I2C Configuration Bus for HDMI Transmitter
set_property -dict { PACKAGE_PIN F18   IOSTANDARD LVCMOS33  PULLUP TRUE } [get_ports { hdmi_scl }];
set_property -dict { PACKAGE_PIN E18   IOSTANDARD LVCMOS33  PULLUP TRUE } [get_ports { hdmi_sda }];

## -----------------------------------------------------------------------------
## 5. UART Serial Debug Interface (Host Link)
## -----------------------------------------------------------------------------
set_property -dict { PACKAGE_PIN C18   IOSTANDARD LVCMOS33 } [get_ports { uart_rx }];
set_property -dict { PACKAGE_PIN C19   IOSTANDARD LVCMOS33 } [get_ports { uart_tx }];

## -----------------------------------------------------------------------------
## 6. Synthesis / Placement Optimization Directives
## -----------------------------------------------------------------------------
## Infer DSP48E1 slices for vector dot products & multiplications
set_property USE_DSP48 "TRUE" [get_cells -hierarchical -filter {NAME =~ *alu_instance* || NAME =~ *vec_alu_instance*}]

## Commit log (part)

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2026-05-02 feat: Phase 1-4 RTL — RV32IM decoder/ALU/registers/PC/LSU, sparsity, ROB
    Agent-Logs-Url: https://github.com/palontologist/tiny-gpu/sessions/5ebe6d8d-5c28-4eb1-afd5-73adee668586
2026-05-02 Changes before error encountered
    Agent-Logs-Url: https://github.com/palontologist/tiny-gpu/sessions/5ebe6d8d-5c28-4eb1-afd5-73adee668586
2026-05-03 feat: Phase 5 L1 cache + Phase 7 128-bit vector extensions (l1_cache, vreg, vec_alu, decoder, lsu, core, gpu, test)
    Agent-Logs-Url: https://github.com/palontologist/tiny-gpu/sessions/4cb9359f-81ee-4464-842e-1309eab086ef
2026-05-03 risc-v
